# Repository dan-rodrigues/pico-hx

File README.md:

# PicoHX

This is an FPGA board that combines an iCE40 HX FPGA with the Raspberry Pi Pico. The Pico can program the FPGA over USB using a script included in this repo and then interact with it using GPIO.

## KiCad rendering

## DVI Demo

Pictured is an included DVI demo. First, the RP2040 was programmed with the USB software which then exposes a USB programmer device to the host. Then, the FPGA configuration containing the DVI test pattern config was uploaded from the host to the RP2040, which then programmed the FPGA, which then displayed the test pattern on screen. [This DVI PMOD](https://1bitsquared.com/collections/fpga/products/pmod-digital-video-interface) was used.

## Features

* iCE40 HX FPGA (TQFP144, 1k pinout assumed)
* 10 Pico GPIOs connected to FPGA
    * 2 are connected to `GBIN` inputs
* 4x PMODs in a 2x double-PMOD arrangement
* 8x user LEDs for FPGA
* 1x CDONE LED
* 2x users buttons for FPGA
* 1x user button for Pico
* `RUN` button for Pico
* Headers for Pico SWD and hardware UART
* Footprint for QSPI PSRAM or flash
* Micro SD card slot

## Design

### Programming

All iCE40 configuration pins are routed to the RP2040 GPIO so the details of how or when it is programmed are up to the software. The included software in this repo will make the Pico present itself is a USB device with these interfaces:

* Vendor programmer interface: This is how the user can program the iCE40 at any time over USB, using the included [picoprog.py](scripts/picoprog.py) script.
* CDC UART: This UART is separate to the hardware UART that is available on the dedicated pin header. By default, `stdout` is sent to the CDC UART for convenience.

### FPGA clock

The pico exposes one pin that can directly output a clock from one of its PLLs with an optional divider. In the demo software, the USB PLL (48MHz) is divided by 4 to output a 12MHz clock for the FPGA. On the FPGA side, the `GBIN5` pin is used for clock input so that the  `SB_PLL40_2F_PAD` can be used.

### Power

There is only a 1.2v regulator on the board as the Pico provides a 3.3v output. The `2V5_VPP` input is tied to 3.3v as the NVCM isn't used in this project.

### PIO support

The 10 GPIOs connected to the FPGA and 4 GPIOs connected to the SD card slot are in consecutive order, so PIO can be used.

## Demo

A demo that displays several test patterns controlled by BTN-A and blinks the LEDs in succession can be found in [rtl/demo](rtl/demo).

```
cd rtl/demo
make prog
```
 
## Usage

### Building Pico software

It's assumed that the [pico-sdk](https://github.com/raspberrypi/pico-sdk) is installed and the required environment variables are set.

```
cd software
mkdir build
cd build
cmake ..
make
```

The software can then be flashed using `picotool` for example. Default behaviour of the software is to immediately flash the iCE40 with an included bitstream that runs a counter with output to the 8 user LEDs.

### Programming iCE40 bitstream

It's assumed that the OSS FPGA toolchain is installed which includes [yosys](https://github.com/YosysHQ/yosys) and [nextpnr-ice40](https://github.com/YosysHQ/nextpnr).

After the Pico software is flashed, it's ready to program the iCE40 using a custom USB driver script. The script is written in Python3 and requires [pyusb](https://github.com/pyusb/pyusb).

```
pip3 install pyusb
```

It can then be programmed with similar usage to [iceprog](https://github.com/YosysHQ/icestorm/tree/master/iceprog). The programmer script is [picoprog.py](scripts/picoprog.py).

```
./picoprog.py bitstream.bit
```

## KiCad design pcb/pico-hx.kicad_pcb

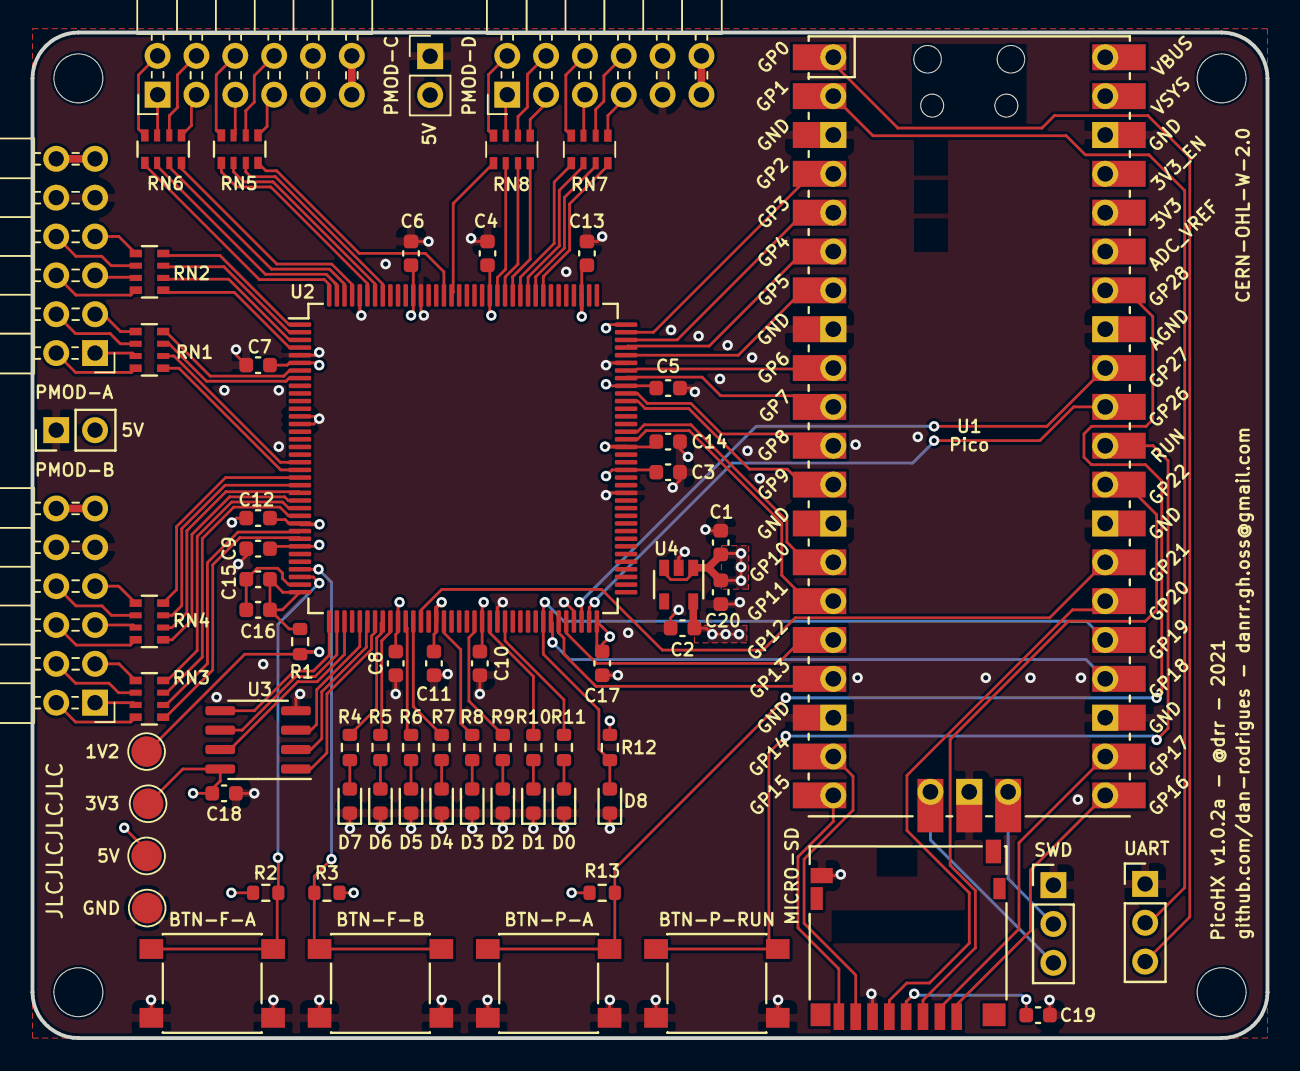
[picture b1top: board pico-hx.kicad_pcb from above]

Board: 4 copper layers, 80.7 x 65.8 mm, 75 parts (0 on the bottom side), 123 nets.

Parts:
C1, C2: 1uF; C_0603_1608Metric
C3, C4, C5, C6, C7, C8, C9, C10, C11, C12, C13, C14, C15, C17, C18: 100nF; C_0603_1608Metric
C16, C19: 10uF; C_0603_1608Metric
C20: 10nF; C_0603_1608Metric
D0, D1, D2, D3, D4, D5, D6, D7: LED; LED_0603_1608Metric
D8: LED_B; LED_0603_1608Metric
H1, H2, H3, H4: MountingHole; MountingHole_3.2mm_M3_DIN965
J1: PMOD_A; PMOD_Double_Mirrored
J2: PMOD_B; PMOD_Double_Mirrored
J3: Micro_SD; microSD_HC_Hirose_DM3D-SF
J4: PMOD_C; PMOD_Double_Mirrored
J5: PMOD_D; PMOD_Double_Mirrored
J6: UART; PinHeader_1x03_P2.54mm_Vertical
J7: RP_SWD; PinHeader_1x03_P2.54mm_Vertical
J8: 5V_AB; PinHeader_1x02_P2.54mm_Vertical
J9: 5V_CD; PinHeader_1x02_P2.54mm_Vertical
R1: 100R; R_0603_1608Metric
R2, R3, R13: 10k; R_0603_1608Metric
R4, R5, R6, R7, R8, R9, R10, R11, R12: 2.2k; R_0603_1608Metric
RN1, RN2, RN3, RN4, RN5, RN6, RN7, RN8: 33R; R_Array_Convex_4x0603
SW1: RUN; SW_SPST_PTS645
SW2: BTN_A; SW_SPST_PTS645
SW3: BTN_B; SW_SPST_PTS645
SW4: BTN_R; SW_SPST_PTS645
TP1: TP_1V2; TestPoint_Pad_D2.0mm
TP2: TP_3V3; TestPoint_Pad_D2.0mm
TP3: TP_5V; TestPoint_Pad_D2.0mm
TP4: TP_GND; TestPoint_Pad_D2.0mm
U1: Pico; RPi_Pico_SMD_TH
U2: ICE40HX1K-TQ144; TQFP-144_20x20mm_P0.5mm
U3: PSRAM; SOIC-8_3.9x4.9mm_P1.27mm
U4: MIC5504-1.2YM5; SOT-23-5

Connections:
+1V2: C2.1, C11.1, C12.1, C13.1, C14.1, R1.1, TP1.1, U2.27, U2.51, U2.92, U2.111, U4.5
+3V3: C3.1, C4.1, C5.1, C6.1, C7.1, C8.1, C9.1, C10.1, C17.1, C18.1, C19.1, J1.6, J1.12, J2.6, J2.12, J3.4, J4.6, J4.12, J5.6, J5.12, R2.1, R3.1, R12.1, R13.1, TP2.1, U1.36, U2.6, U2.30, U2.46, U2.57, U2.72, U2.89, U2.100, U2.108, U2.123, U2.133, U3.8
+5V: C1.1, C20.1, J8.2, J9.2, TP3.1, U1.40, U4.1, U4.3
/BTN_A: R2.2, SW2.1, U2.34
/BTN_B: R3.2, SW3.1, U2.33
/BTN_P: R13.2, SW4.1, U1.34
/FPGA_CDONE: D8.2, R12.2, U1.25, U2.65
/FPGA_CLK: U1.27, U2.49
/FPGA_GNDPLL: C15.2, C16.2, U2.35
/FPGA_RPIO_0: U1.4, U2.107
/FPGA_RPIO_1: U1.5, U2.106
/FPGA_RPIO_2: U1.6, U2.105
/FPGA_RPIO_3: U1.7, U2.104
/FPGA_RPIO_4: U1.9, U2.102
/FPGA_RPIO_5: U1.10, U2.101
/FPGA_RPIO_6: U1.11, U2.99
/FPGA_RPIO_7: U1.12, U2.98
/FPGA_RPIO_S0: U1.14, U2.94
/FPGA_RPIO_S1: U1.15, U2.93
/FPGA_SCK: U1.32, U2.70
/FPGA_SDI: U1.16, U2.68
/FPGA_SDO: U1.17, U2.67
/FPGA_SS: U1.31, U2.71
/FPGA_VCCPLL: C15.1, C16.1, R1.2, U2.36
/LED_0: R11.1, U2.60
/LED_1: R10.1, U2.58
/LED_2: R9.1, U2.56
/LED_3: R8.1, U2.52
/LED_4: R7.1, U2.48
/LED_5: R6.1, U2.47
/LED_6: R5.1, U2.45
/LED_7: R4.1, U2.44
/PMOD_A1: RN1.6, U2.19
/PMOD_A2: RN1.8, U2.7
/PMOD_A3: RN2.6, U2.3
/PMOD_A4: RN2.8, U2.1
/PMOD_A7: RN1.5, U2.20
/PMOD_A8: RN1.7, U2.8
/PMOD_A9: RN2.5, U2.4
/PMOD_A10: RN2.7, U2.2
/PMOD_B1: RN3.6, U2.28
/PMOD_B2: RN3.8, U2.25
/PMOD_B3: RN4.6, U2.23
/PMOD_B4: RN4.8, U2.21
/PMOD_B7: RN3.5, U2.29
/PMOD_B8: RN3.7, U2.26
/PMOD_B9: RN4.5, U2.24
/PMOD_B10: RN4.7, U2.22
/PMOD_C1: RN6.6, U2.143
/PMOD_C2: RN6.8, U2.141
/PMOD_C3: RN5.6, U2.138
/PMOD_C4: RN5.8, U2.129
/PMOD_C7: RN6.5, U2.144
/PMOD_C8: RN6.7, U2.142
/PMOD_C9: RN5.5, U2.139
/PMOD_C10: RN5.7, U2.137
/PMOD_D1: RN8.6, U2.122
/PMOD_D2: RN8.8, U2.120
/PMOD_D3: RN7.6, U2.118
/PMOD_D4: RN7.8, U2.116
/PMOD_D7: RN8.5, U2.128
/PMOD_D8: RN8.7, U2.121
/PMOD_D9: RN7.5, U2.119
/PMOD_D10: RN7.7, U2.117
/PSRAM_SCK: U2.38, U3.6
/PSRAM_SI: U2.37, U3.5
/PSRAM_SIO2: U2.41, U3.3
/PSRAM_SIO3: U2.39, U3.7
/PSRAM_SO: U2.42, U3.2
/RP_SWCLK: J7.3, U1.41
/RP_SWDIO: J7.2, U1.43
/SD_CLK: J3.5, U1.26
/SD_CMD: J3.3, U1.29
/SD_DAT0: J3.7, U1.19
/SD_DAT1: J3.8, U1.20
/SD_DAT2: J3.1, U1.21
/SD_DAT3: J3.2, U1.22
/UART_RX: J6.2, U1.2
/UART_TX: J6.3, U1.1
/~FPGA_CRESET: U1.24, U2.66
/~PSRAM_CS: U2.43, U3.1
GND: C1.2, C2.2, C3.2, C4.2, C5.2, C6.2, C7.2, C8.2, C9.2, C10.2, C11.2, C12.2, C13.2, C14.2, C17.2, C18.2, C19.2, C20.2, D0.1, D1.1, D2.1, D3.1, D4.1, D5.1, D6.1, D7.1, D8.1, J1.5, J1.11, J2.5, J2.11, J3.6, J3.9, J4.5, J4.11, J5.5, J5.11, J6.1, J7.1, J8.1, J9.1, SW1.2, SW2.2, SW3.2, SW4.2, TP4.1, U1.3, U1.8, U1.13, U1.18, U1.23, U1.28, U1.33, U1.38, U1.42, U2.5, U2.13, U2.14, U2.59, U2.69, U2.86, U2.103, U2.132, U2.140, U3.4, U4.2
unnamed: D0.2, R11.2
unnamed: D1.2, R10.2
unnamed: D2.2, R9.2
unnamed: D3.2, R8.2
unnamed: D4.2, R7.2
unnamed: D5.2, R6.2
unnamed: D6.2, R5.2
unnamed: D7.2, R4.2
unnamed: J1.1, RN1.3
unnamed: J1.2, RN1.1
unnamed: J1.3, RN2.3
unnamed: J1.4, RN2.1
unnamed: J1.7, RN1.4
unnamed: J1.8, RN1.2
unnamed: J1.9, RN2.4
unnamed: J1.10, RN2.2
unnamed: J2.1, RN3.3
unnamed: J2.2, RN3.1
unnamed: J2.3, RN4.3
unnamed: J2.4, RN4.1
unnamed: J2.7, RN3.4
unnamed: J2.8, RN3.2
unnamed: J2.9, RN4.4
unnamed: J2.10, RN4.2
unnamed: J4.1, RN6.3
unnamed: J4.2, RN6.1
unnamed: J4.3, RN5.3
unnamed: J4.4, RN5.1
unnamed: J4.7, RN6.4
unnamed: J4.8, RN6.2
unnamed: J4.9, RN5.4
unnamed: J4.10, RN5.2
unnamed: J5.1, RN8.3
unnamed: J5.2, RN8.1
unnamed: J5.3, RN7.3
unnamed: J5.4, RN7.1
unnamed: J5.7, RN8.4
unnamed: J5.8, RN8.2
unnamed: J5.9, RN7.4
unnamed: J5.10, RN7.2
unnamed: SW1.1, U1.30

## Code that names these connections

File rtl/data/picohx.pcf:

# Clock from RP2040

set_io clk_in 49

# LEDs

set_io led[0] 60
set_io led[1] 58
set_io led[2] 56
set_io led[3] 52
set_io led[4] 48
set_io led[5] 47
set_io led[6] 45
set_io led[7] 44

# Buttons

set_io btn_a 34
set_io btn_b 33

# PSRAM / Flash

set_io psram_sck 38
set_io psram_csn 43
set_io psram_io[0] 37
set_io psram_io[1] 42
set_io psram_io[2] 41
set_io psram_io[3] 39

# RP2040 GPIO

set_io rp_io[0] 107
set_io rp_io[1] 106
set_io rp_io[2] 105
set_io rp_io[3] 104
set_io rp_io[4] 102
set_io rp_io[5] 101
set_io rp_io[6] 99
set_io rp_io[7] 98

set_io rp_sio[0] 94
set_io rp_sio[1] 93

# PMOD-A

set_io pmod_a1 19
set_io pmod_a2 7
set_io pmod_a3 3
set_io pmod_a4 1
set_io pmod_a7 20
set_io pmod_a8 8
set_io pmod_a9 4
set_io pmod_a10 2

# PMOD-B

set_io pmod_b1 28
set_io pmod_b2 25
set_io pmod_b3 23
set_io pmod_b4 21
set_io pmod_b7 29
set_io pmod_b8 26
set_io pmod_b9 24
set_io pmod_b10 22

# PMOD-C

set_io pmod_c1 143
set_io pmod_c2 141
set_io pmod_c3 138
set_io pmod_c4 129
set_io pmod_c7 144
set_io pmod_c8 142
set_io pmod_c9 139
set_io pmod_c10 137

# PMOD-D

set_io pmod_d1 122
set_io pmod_d2 120
set_io pmod_d3 118
set_io pmod_d4 116
set_io pmod_d7 128
set_io pmod_d8 121
set_io pmod_d9 119
set_io pmod_d10 117

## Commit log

2021-05-01 Restore repo
2021-05-01 misc: add licenses
2021-05-02 doc: few more details on the README
2021-05-03 scripts: correct header with filename
2021-05-03 doc: fix picoprog.py links
2021-05-04 misc: ignore transient files
2021-05-07 rtl: add video demo
2021-05-07 doc: add partial PCB assembly photo
2021-05-12 pcb: reverse LED order to be more intuitive
    Previously the LSB was on the right and the MSB was on left.
    Outputting an 8bit value for example would be confusing if interpreting it as a binary representation.
2021-08-29 pcb: add copper-keepout for SD card connector
2021-08-29 doc: remove "WIP" qualifier since board was tested
2021-08-29 doc: added more context around the demo

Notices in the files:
pcb/pico-hx.kicad_pcb:
CERN-OHL-W-2.0
